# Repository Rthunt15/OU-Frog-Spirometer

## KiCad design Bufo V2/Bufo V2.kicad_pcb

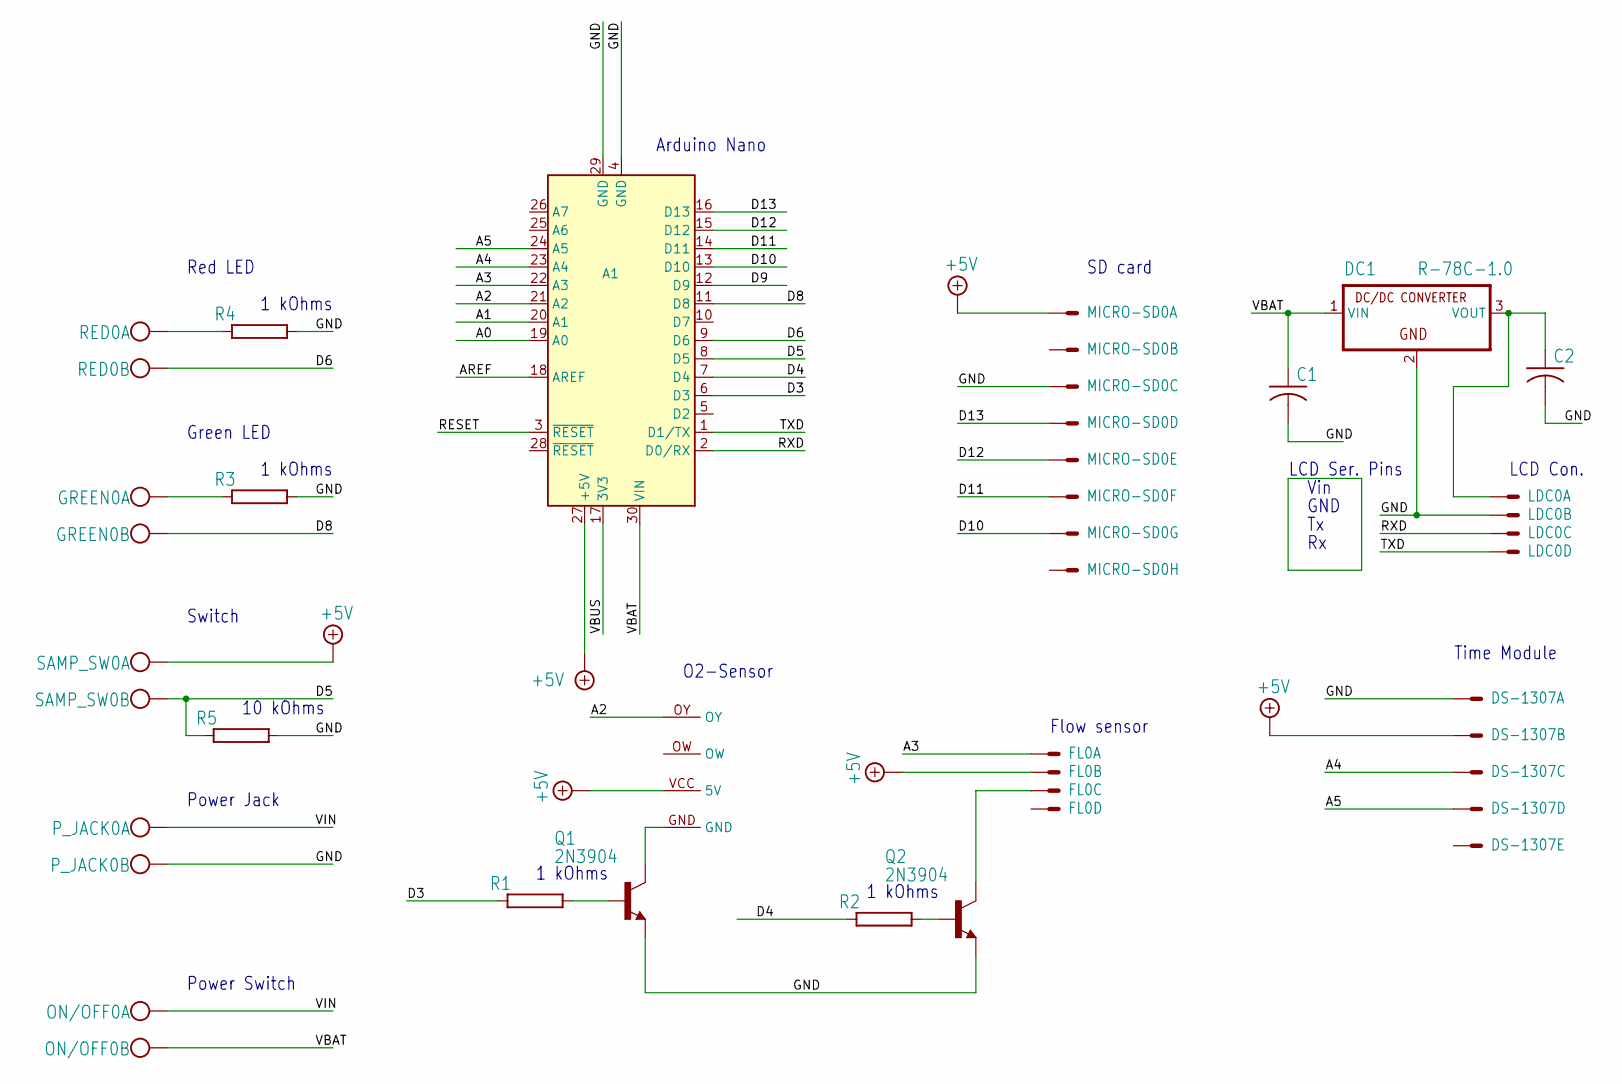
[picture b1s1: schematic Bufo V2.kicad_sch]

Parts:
A1: Arduino_Nano_v2.x; Arduino_Nano
C1, C2: C-US025-024X044; C025-024X044
DC1: R-78C-1.0; SIP3
DS-1307: 22-?-0527-2051; 6410-05
FL0: 22-23-2041
GREEN0: W237-102
LDC0: 22-23-2041
MICRO-SD0: 22-?-0827-2081; 6410-08
ON/OFF0: W237-102
P_JACK0: W237-102
Q1, Q2: 2N3904; TO92
R1, R2, R3, R4, R5: RAC01; AC01
RED0: W237-102
SAMP_SW0: W237-102
U$1: UNI-4

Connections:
+5V: A1.27 (+5V), DS-1307.2 (S), FL0.2 (S), MICRO-SD0.1 (S), SAMP_SW0.1 (KL), U$1.VCC (5V); also elsewhere on the board
/A2: A1.21 (A2), U$1.OY; also elsewhere on the board
/A3: A1.22 (A3), FL0.1 (S); also elsewhere on the board
/A4: A1.23 (A4), DS-1307.3 (S); also elsewhere on the board
/A5: A1.24 (A5), DS-1307.4 (S); also elsewhere on the board
/D3: A1.6 (D3), R1.1; also elsewhere on the board
/D4: A1.7 (D4), R2.1; also elsewhere on the board
/D5: A1.8 (D5), R5.1, SAMP_SW0.2 (KL); also elsewhere on the board
/D6: A1.9 (D6), RED0.2 (KL); also elsewhere on the board
/D8: A1.11 (D8), GREEN0.2 (KL); also elsewhere on the board
/D10: A1.13 (D10), MICRO-SD0.7 (S); also elsewhere on the board
/D11: A1.14 (D11), MICRO-SD0.6 (S); also elsewhere on the board
/D12: A1.15 (D12), MICRO-SD0.5 (S); also elsewhere on the board
/D13: A1.16 (D13), MICRO-SD0.4 (S); also elsewhere on the board
/GND: A1.4 (GND), A1.29 (GND), C1.2, C2.2, DC1.2 (GND), DS-1307.1 (S), LDC0.2 (S), MICRO-SD0.3 (S), P_JACK0.2 (KL), Q1.3 (E), Q2.3 (E), R3.2, R4.2, R5.2; also elsewhere on the board
/RXD: A1.2 (D0/RX), LDC0.3 (S); also elsewhere on the board
/TXD: A1.1 (D1/TX), LDC0.4 (S); also elsewhere on the board
/VBAT: A1.30 (VIN), C1.1, DC1.1 (VIN), ON/OFF0.2 (KL); also elsewhere on the board
/VIN: ON/OFF0.1 (KL), P_JACK0.1 (KL)
unnamed: C2.1, DC1.3 (VOUT), LDC0.1 (S)
unnamed: FL0.3 (S), Q2.1 (C)
unnamed: GREEN0.1 (KL), R3.1
unnamed: Q1.2 (B), R1.2
unnamed: Q1.1 (C), U$1.GND
unnamed: Q2.2 (B), R2.2
unnamed: R4.1, RED0.1 (KL)

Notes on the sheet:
Red LED
LCD Con.
1 kOhms
Flow sensor
Green LED
LCD Ser. Pins
Vin
O2-Sensor
SD card
10 kOhms
Power Jack
Time Module
Arduino Nano
Switch
Power Switch
GND

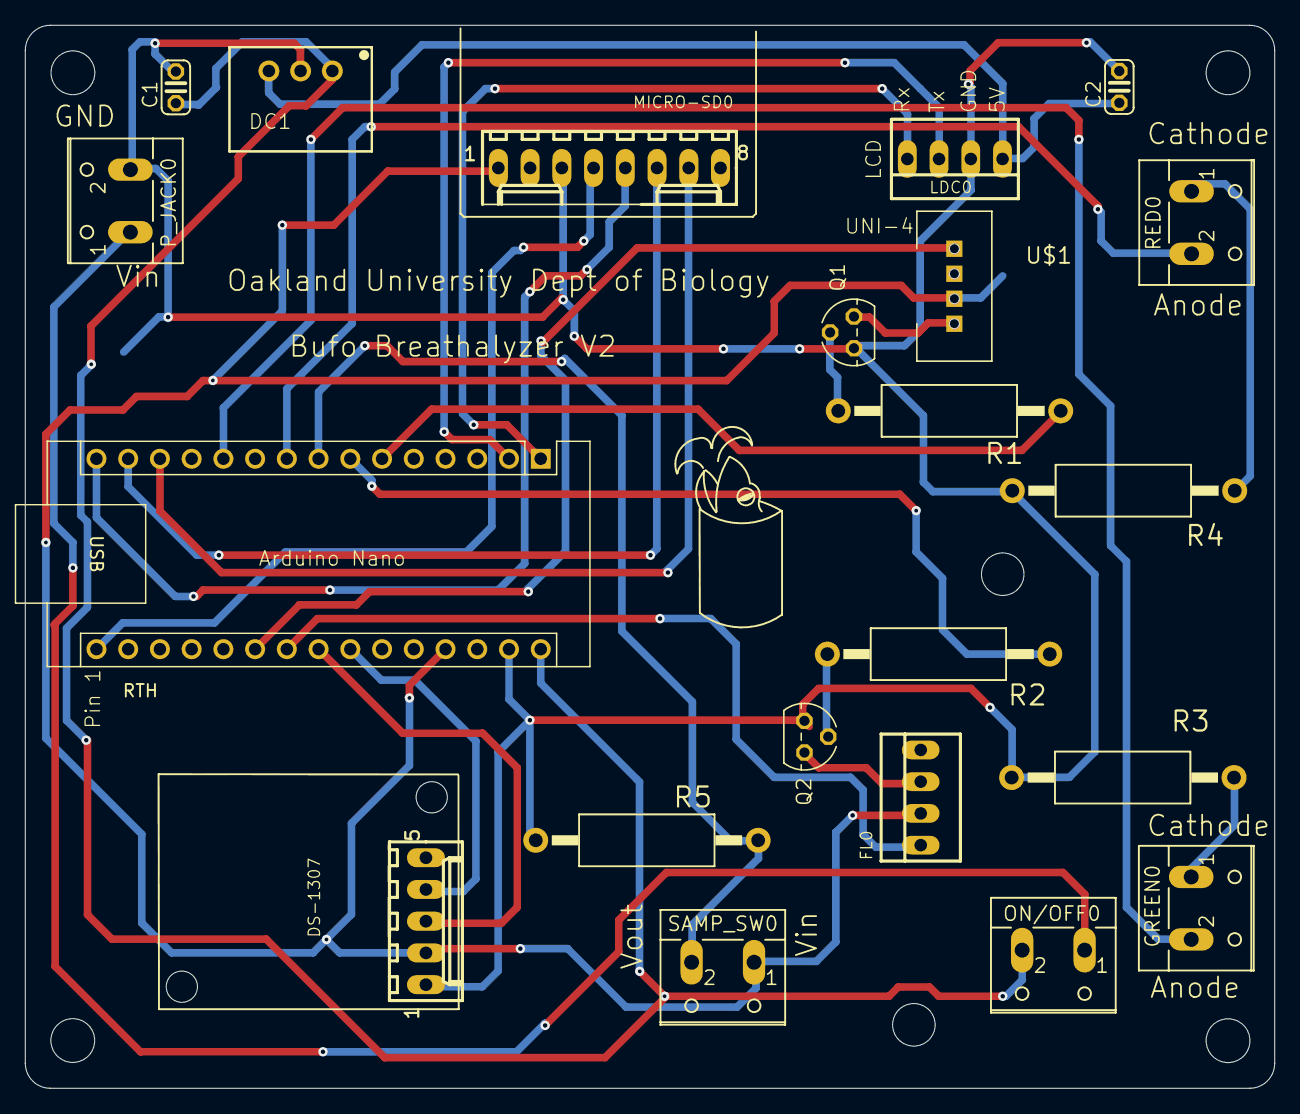
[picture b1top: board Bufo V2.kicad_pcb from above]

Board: 2 copper layers, 100.0 x 85.1 mm, 29 parts (0 on the bottom side), 26 nets.

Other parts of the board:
@HOLE0, @HOLE1, @HOLE2, @HOLE3, @HOLE4, @HOLE5, @HOLE6, @HOLE7: (no value)
RTH: Arduino_Nano_v2.x; Arduino_Nano

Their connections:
+5V: RTH.27 (+5V); also elsewhere on the board
/A2: RTH.21 (A2); also elsewhere on the board
/A3: RTH.22 (A3); also elsewhere on the board
/A4: RTH.23 (A4); also elsewhere on the board
/A5: RTH.24 (A5); also elsewhere on the board
/D3: RTH.6 (D3); also elsewhere on the board
/D4: RTH.7 (D4); also elsewhere on the board
/D5: RTH.8 (D5); also elsewhere on the board
/D6: RTH.9 (D6); also elsewhere on the board
/D8: RTH.11 (D8); also elsewhere on the board
/D10: RTH.13 (D10); also elsewhere on the board
/D11: RTH.14 (D11); also elsewhere on the board
/D12: RTH.15 (D12); also elsewhere on the board
/D13: RTH.16 (D13); also elsewhere on the board
/GND: RTH.29 (GND); also elsewhere on the board
/RXD: RTH.2 (D0/RX); also elsewhere on the board
/TXD: RTH.1 (D1/TX); also elsewhere on the board
/VBAT: RTH.30 (VIN); also elsewhere on the board

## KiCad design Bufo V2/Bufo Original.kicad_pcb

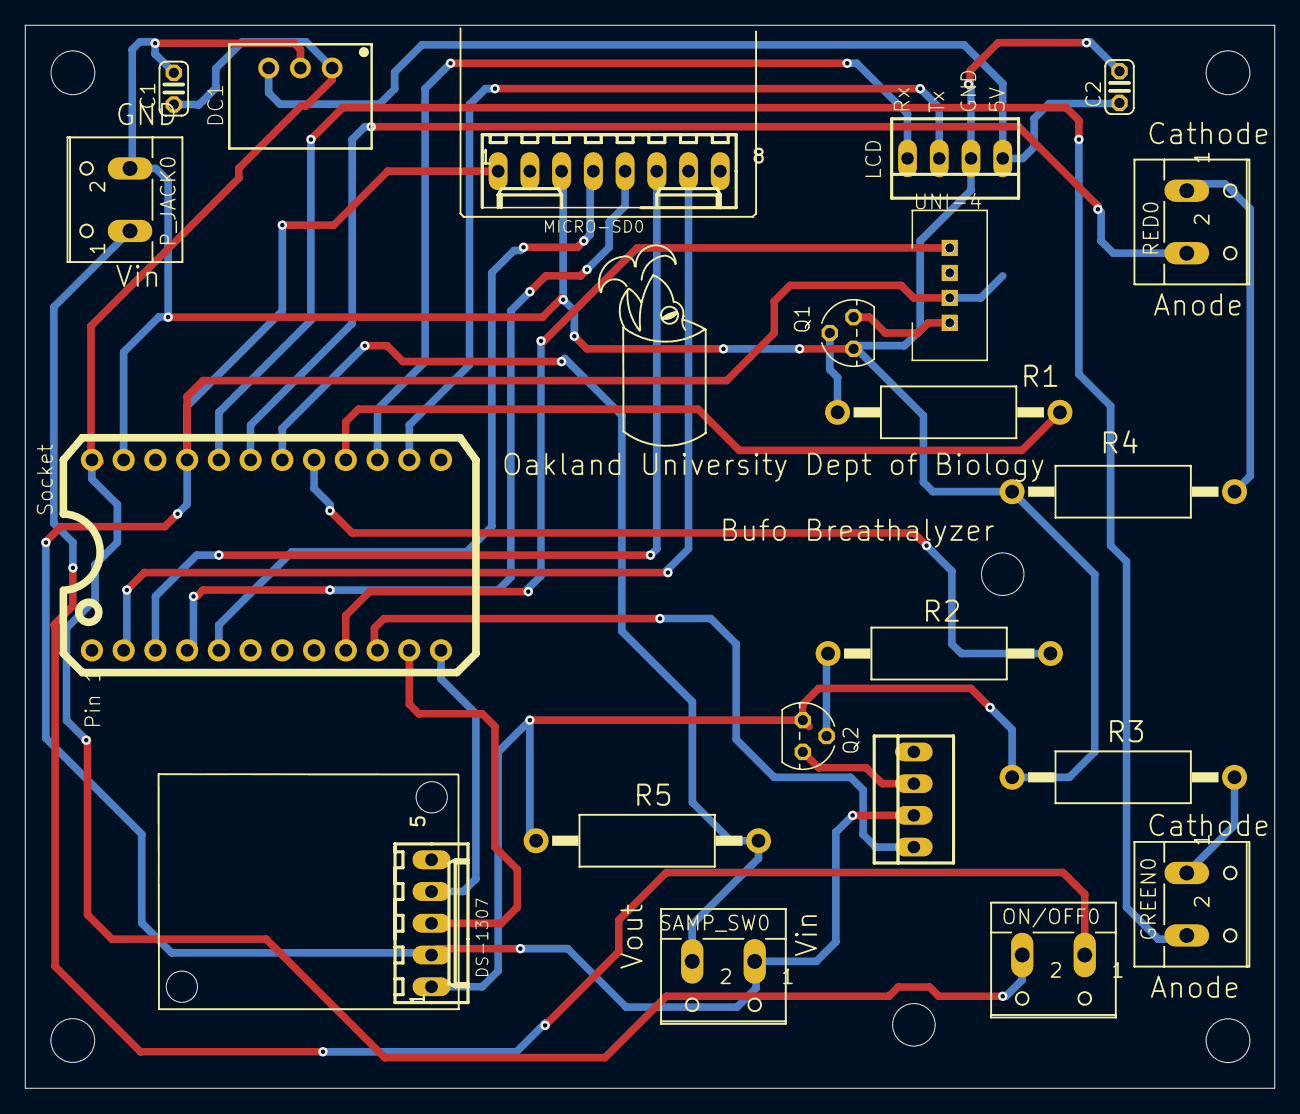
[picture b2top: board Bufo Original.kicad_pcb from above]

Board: 2 copper layers, 100.0 x 85.1 mm, 30 parts (0 on the bottom side), 26 nets.

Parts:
@HOLE0, @HOLE1, @HOLE2, @HOLE3, @HOLE4, @HOLE5, @HOLE6, @HOLE7: (no value)
C1, C2: C025-024X044
DC1: R-78C1.8-1.0; SIP3
DS-1307: 22-27-2051-05; 6410-05
FL0: 22-23-2041
GREEN0: W237-102
JP1, JP4: 1X12-CB
LDC0: 22-23-2041
MICRO-SD0: 22-27-2081-08; 6410-08
ON/OFF0: W237-102
P_JACK0: W237-102
Q1, Q2: 2N3904; TO92
R1, R2, R3, R4, R5: AC01
RED0: W237-102
SAMP_SW0: W237-102
U$1: UNI-4

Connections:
+5V: DS-1307.2, FL0.2, JP1.4, MICRO-SD0.1, SAMP_SW0.1, U$1.VCC
A2: JP4.9, U$1.OY
A3: FL0.1, JP4.10
A4: DS-1307.3, JP4.11
A5: DS-1307.4, JP4.12
D3: JP1.9, R1.1
D4: JP1.8, R2.1
D5: JP1.7, R5.1, SAMP_SW0.2
D6: JP1.6, RED0.2
D8: GREEN0.2, JP1.5
D10: JP4.2, MICRO-SD0.7
D11: JP4.3, MICRO-SD0.6
D12: JP4.4, MICRO-SD0.5
D13: JP4.5, MICRO-SD0.4
GND: C1.2, C2.2, DC1.2, DS-1307.1, JP1.2, LDC0.2, MICRO-SD0.3, P_JACK0.2, Q1.3, Q2.3, R3.2, R4.2, R5.2
unnamed: Q1.2, R1.2
unnamed: Q2.2, R2.2
unnamed: Q1.1, U$1.GND
unnamed: FL0.3, Q2.1
unnamed: R4.1, RED0.1
unnamed: GREEN0.1, R3.1
unnamed: C2.1, DC1.3, LDC0.1
RXD: JP1.11, LDC0.3
TXD: JP1.10, LDC0.4
VBAT: C1.1, DC1.1, JP1.1, ON/OFF0.2
VIN: ON/OFF0.1, P_JACK0.1
